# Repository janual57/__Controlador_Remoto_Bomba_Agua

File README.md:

# __Controlador_WiFi_Bomba_Agua
 Controlador WiFi Bomba Agua

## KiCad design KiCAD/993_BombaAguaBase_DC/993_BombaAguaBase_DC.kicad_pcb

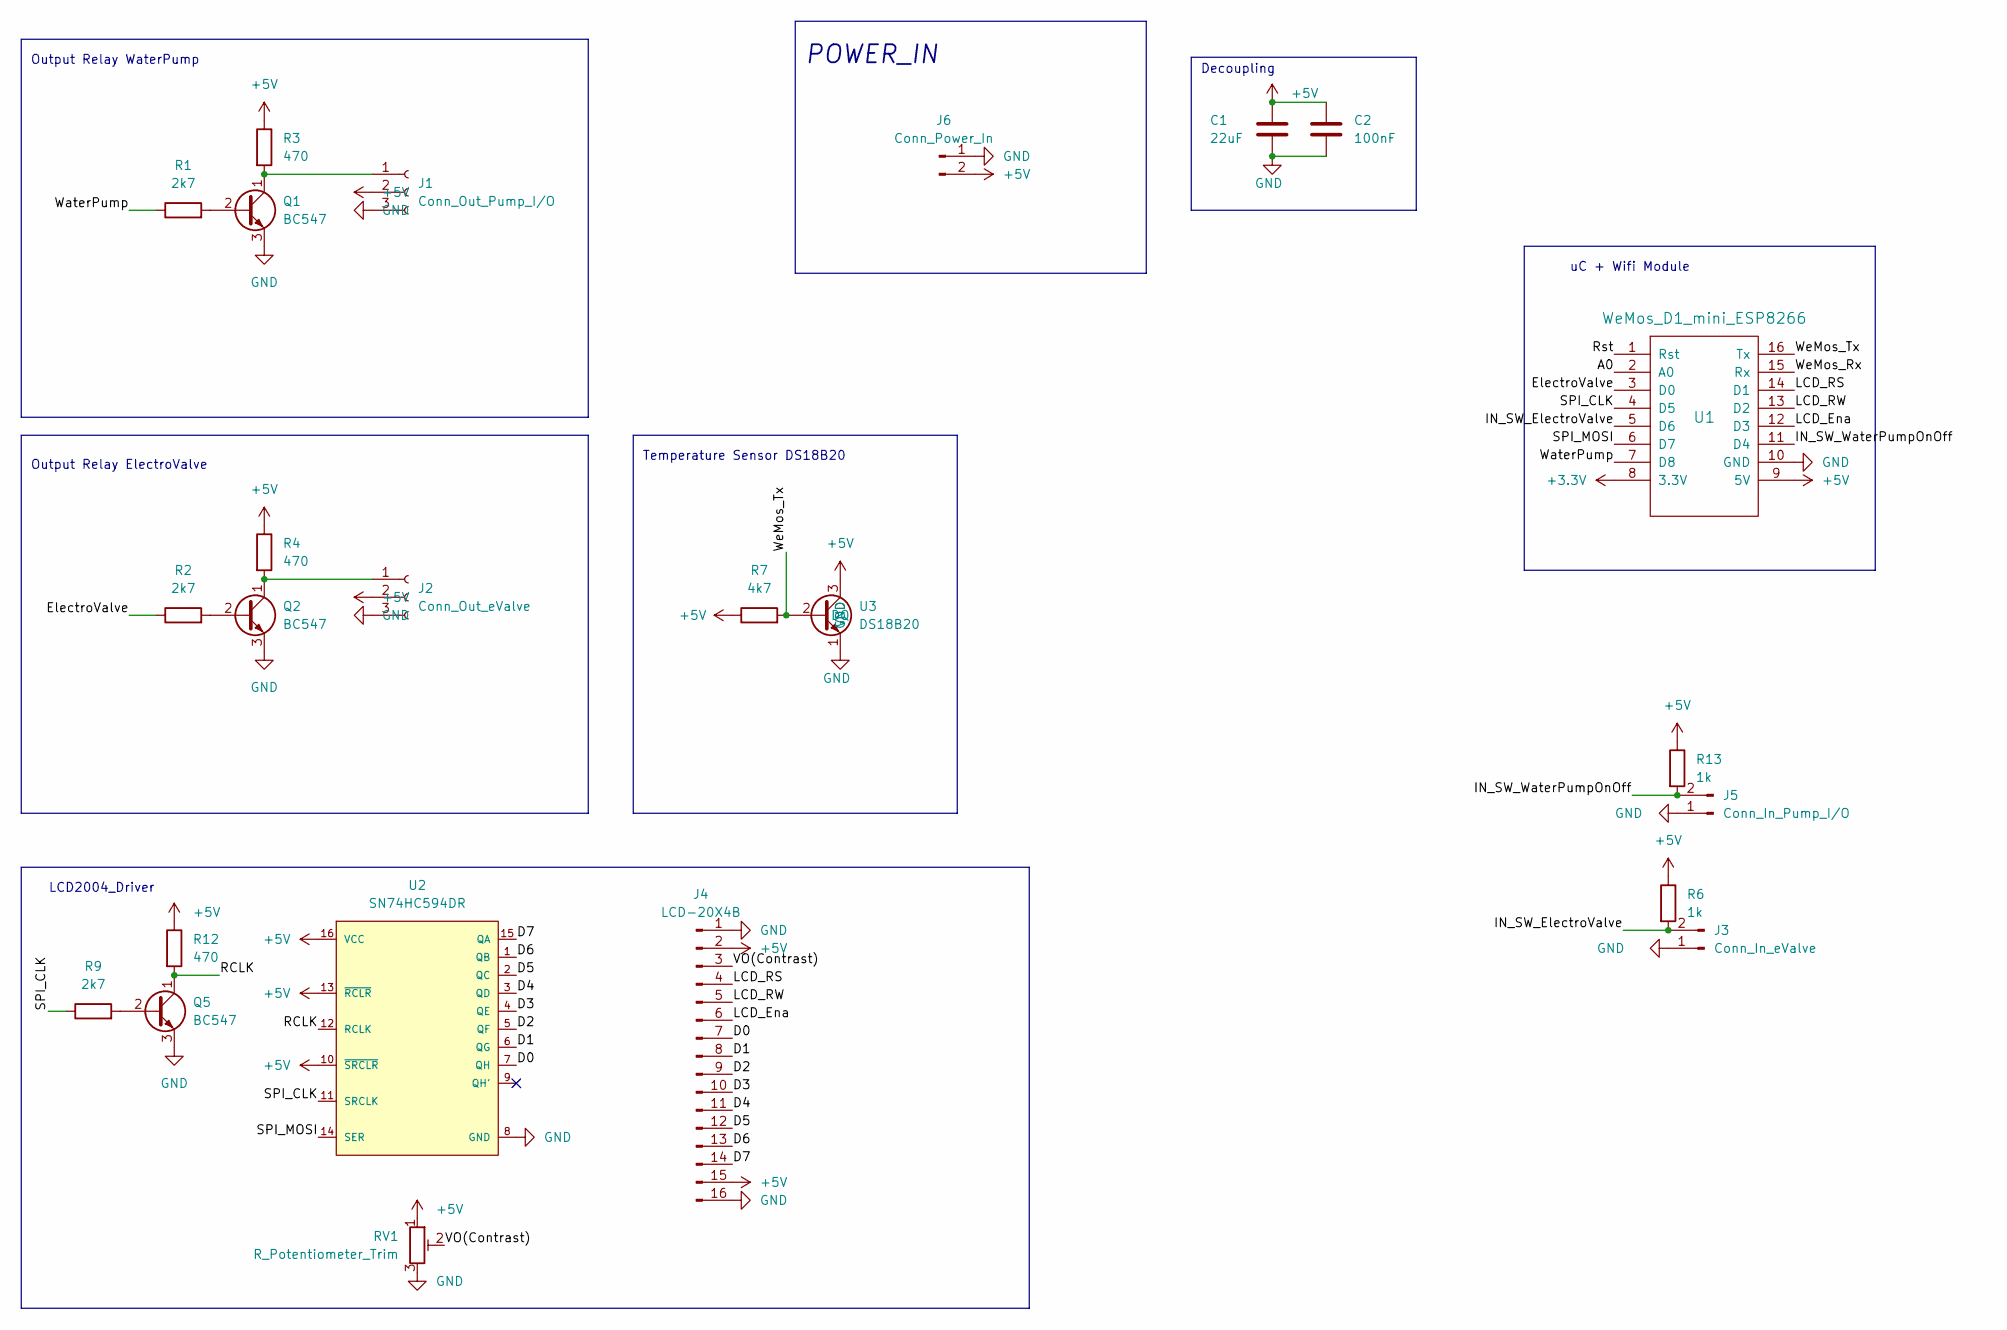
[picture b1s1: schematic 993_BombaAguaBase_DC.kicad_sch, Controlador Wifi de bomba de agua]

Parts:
C1: 22uF; CP_Radial_D10.0mm_P2.50mm
C2: 100nF; C_Disc_D3.8mm_W2.6mm_P2.50mm
J1: Conn_Out_Pump_I/O; JST_EH_B3B-EH-A_1x03_P2.50mm_Vertical
J2: Conn_Out_eValve; JST_EH_B3B-EH-A_1x03_P2.50mm_Vertical
J3: Conn_In_eValve; JST_EH_B2B-EH-A_1x02_P2.50mm_Vertical
J4: LCD-20X4B; PinHeader_1x16_P2.54mm_Vertical
J5: Conn_In_Pump_I/O; JST_EH_B2B-EH-A_1x02_P2.50mm_Vertical
J6: Conn_Power_In; JST_EH_B2B-EH-A_1x02_P2.50mm_Vertical
Q1, Q2, Q5: BC547; TO-92_Inline_Wide
R1, R2, R9: 2k7; R_Axial_DIN0207_L6.3mm_D2.5mm_P7.62mm_Horizontal
R3, R4, R12: 470; R_Axial_DIN0207_L6.3mm_D2.5mm_P7.62mm_Horizontal
R6, R13: 1k; R_Axial_DIN0207_L6.3mm_D2.5mm_P7.62mm_Horizontal
R7: 4k7; R_Axial_DIN0207_L6.3mm_D2.5mm_P7.62mm_Horizontal
RV1: R_Potentiometer_Trim; Potentiometer_Bourns_3296W_Vertical
U1: WeMos_D1_mini_ESP8266; D1_mini_board
U2: SN74HC594DR; DIP-16_W7.62mm; mouser part number 595-SN74HC594DR; digikey description IC SHIFT REGISTER 8BIT 16-SOIC
U3: DS18B20; TO-92_Inline_Wide

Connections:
+3.3V: U1.8 (3.3V)
+5V: C1.1, C2.1, J1.2, J2.2, J4.2, J4.15, J6.2, R3.1, R4.1, R6.1, R7.1, R12.1, R13.1, RV1.1, U1.9 (5V), U2.10 (~SRCLR), U2.13 (~RCLR), U2.16 (VCC), U3.3 (VDD)
/A0: U1.2 (A0)
/D0: J4.7, U2.7 (QH)
/D1: J4.8, U2.6 (QG)
/D2: J4.9, U2.5 (QF)
/D3: J4.10, U2.4 (QE)
/D4: J4.11, U2.3 (QD)
/D5: J4.12, U2.2 (QC)
/D6: J4.13, U2.1 (QB)
/D7: J4.14, U2.15 (QA)
/ElectroValve: R2.1, U1.3 (D0)
/IN_SW_ElectroValve: J3.2, R6.2, U1.5 (D6)
/IN_SW_WaterPumpOnOff: J5.2, R13.2, U1.11 (D4)
/LCD_Ena: J4.6, U1.12 (D3)
/LCD_RS: J4.4, U1.14 (D1)
/LCD_RW: J4.5, U1.13 (D2)
/RCLK: Q5.1 (C), R12.2, U2.12 (RCLK)
/Rst: U1.1 (Rst)
/SPI_CLK: R9.1, U1.4 (D5), U2.11 (SRCLK)
/SPI_MOSI: U1.6 (D7), U2.14 (SER)
/VO(Contrast): J4.3, RV1.2
/WaterPump: R1.1, U1.7 (D8)
/WeMos_Rx: U1.15 (Rx)
/WeMos_Tx: R7.2, U1.16 (Rx), U3.2 (DQ)
GND: C1.2, C2.2, J1.3, J2.3, J3.1, J4.1, J4.16, J5.1, J6.1, Q1.3 (E), Q2.3 (E), Q5.3 (E), RV1.3, U1.10 (GND), U2.8 (GND), U3.1 (GND)
unnamed: J1.1, Q1.1 (C), R3.2
unnamed: J2.1, Q2.1 (C), R4.2
unnamed: Q1.2 (B), R1.2
unnamed: Q2.2 (B), R2.2
unnamed: Q5.2 (B), R9.2

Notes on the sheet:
LCD2004_Driver
Decoupling
POWER_IN
Temperature Sensor DS18B20
Output Relay WaterPump
uC + Wifi Module
Output Relay ElectroValve

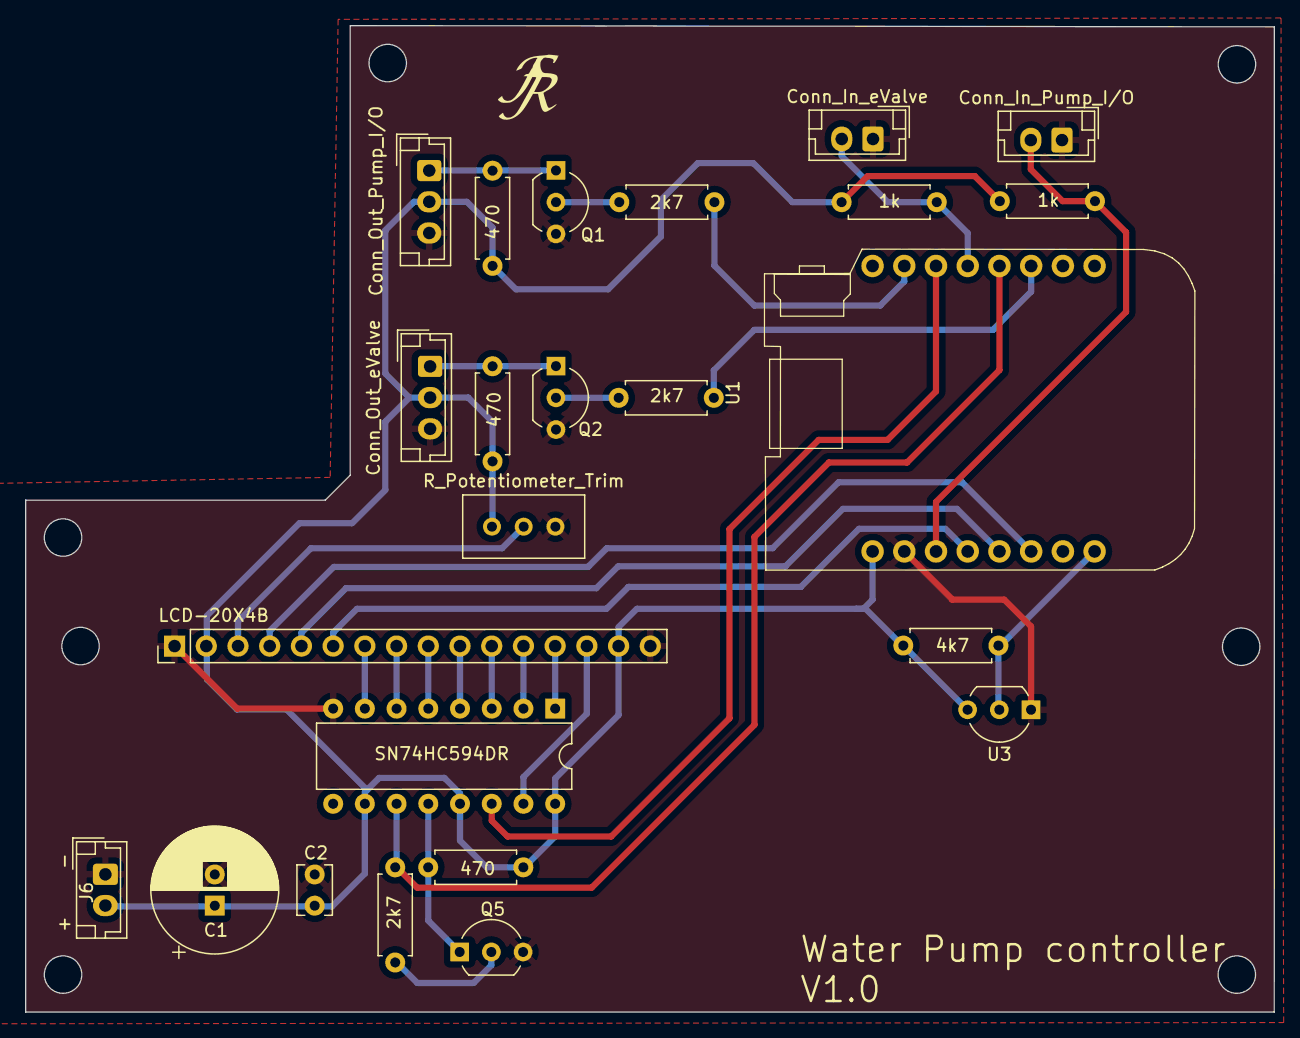
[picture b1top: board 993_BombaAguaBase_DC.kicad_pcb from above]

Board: 2 copper layers, 100.0 x 79.0 mm, 24 parts (0 on the bottom side), 27 nets.

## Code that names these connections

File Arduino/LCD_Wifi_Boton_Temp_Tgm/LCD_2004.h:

#ifndef LCD_2004_h
#define LCD_2004_h

#include "Arduino.h"

#define LCD_Data D7
#define LCD_Clk D5
#define LCD_Ena D3
#define LCD_RW D2
#define LCD_RS D1

// the #include statement and code go here...
void LCD2004_Init();

  //Start LCD initialization
  //LCD2004_Test(hspi1);
  //Function Set
  //0 0 1 DL N F X X :: DL=1= 8bit; N=1=2LineDisplay; F=0=5x8dots ::0x38
void LCD2004_FunctionSet();

  //Clear Display
  //0x01
void LCD2004_ClearScreen();

  //Return Home
  //0x02
void LCD2004_ReturnHome();

  //DisplayOnOffControl
  //0 0 0 0 1 D C B :: D=1=Display ON; C=1=CursorON ; B=1=CursorBlink ::0x0F
void LCD2004_DisplayOnOffControl();

/*
 *rPos needs to be within below range
 *0x00 -> Line1/Row1 :: 0x4F -> Line4/Row20
 */
void LCD2004_SetCursor(uint8_t rPos);

void LCD2004_WriteChar(uint8_t sChar);

void LCD2004_WriteString(uint8_t * sString);

void LCD2004_WriteTittle(uint8_t * sString);

void LCD2004_WriteMainLabel(uint8_t * sString);

void LCD2004_WriteSubLabel(uint8_t * sString);

void LCD2004_WriteMessage(uint8_t * sString);

void LCD2004_CleanLine(uint8_t rPos);

void LCD2004_WelcomeScreen();
#endif

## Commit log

2024-05-11 Initial Commit
    Upload of
    Media
    BOM
    Arduino
    FreeCAD
    KiCAD
2024-07-06 Timer added
    Added Timer (ms) to auto stop (from Power On to Power Off)
